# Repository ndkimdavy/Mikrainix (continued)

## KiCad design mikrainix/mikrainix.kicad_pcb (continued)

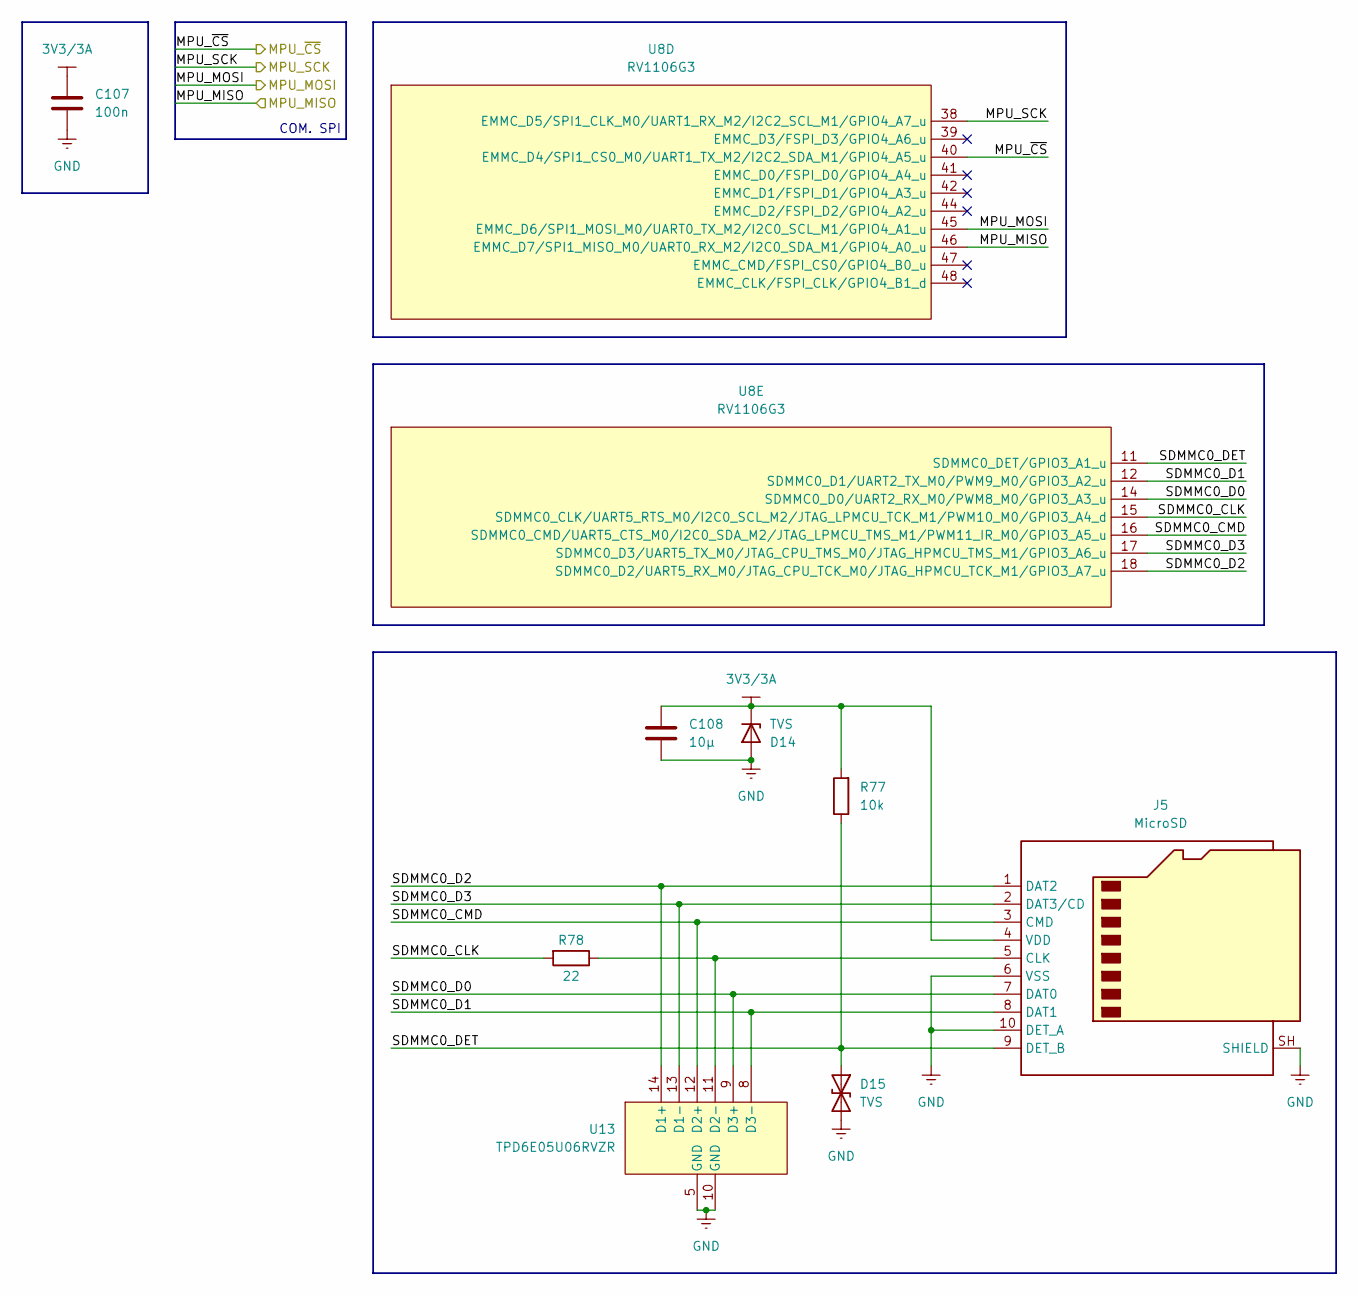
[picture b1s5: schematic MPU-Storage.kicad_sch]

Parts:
C107: 100n; C_0402_1005Metric
C108: 10µ; C_0805_2012Metric
D14: TVS; D_SMB; MPN SMLVT3V3
D15: TVS; DIO_TPD1E10B06DPYR; MPN TPD1E10B06DPYR
J5: MicroSD; microSD_HC_Hirose_DM3AT-SF-PEJM5
R77: 10k; R_0402_1005Metric
R78: 22; R_0402_1005Metric
U8: RV1106G3; QFN35P1230X1230X90-129N
U13: TPD6E05U06RVZR; RVZ0014A

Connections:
3V3/3A: C107.1, C108.1, D14.1 (K), J5.4 (VDD), R77.2; also elsewhere on the board
/U_FPGA-Ctrl/FPGA_MISO: U8.46 (EMMC_D7/SPI1_MISO_M0/UART0_RX_M2/I2C0_S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); also elsewhere on the board
/U_FPGA-Ctrl/FPGA_MOSI: U8.45 (EMMC_D6/SPI1_MOSI_M0/UART0_TX_M2/I2C0_S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); also elsewhere on the board
/U_FPGA-Ctrl/FPGA_SCK: U8.38 (EMMC_D5/SPI1_CLK_M0/UART1_RX_M2/I2C2_SC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); also elsewhere on the board
/U_FPGA-Ctrl/FPGA_~CS: U8.40 (EMMC_D4/SPI1_CS0_M0/UART1_TX_M2/I2C2_SD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); also elsewhere on the board
/U_MPU-Storage/SDMMC0_CLK: R78.2, U8.15 (SDMMC0_CLK/UART5_RTS_M0/I2C0_SCL_M2/JTA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)
/U_MPU-Storage/SDMMC0_CMD: J5.3 (CMD), U8.16 (SDMMC0_CMD/UART5_CTS_M0/I2C0_SDA_M2/JTA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), U13.12 (D2+)
/U_MPU-Storage/SDMMC0_D0: J5.7 (DAT0), U8.14 (SDMMC0_D0/UART2_RX_M0/PWM8_M0/GPIO3_A3_u), U13.9 (D3+)
/U_MPU-Storage/SDMMC0_D1: J5.8 (DAT1), U8.12 (SDMMC0_D1/UART2_TX_M0/PWM9_M0/GPIO3_A2_u), U13.8 (D3-)
/U_MPU-Storage/SDMMC0_D2: J5.1 (DAT2), U8.18 (SDMMC0_D2/UART5_RX_M0/JTAG_CPU_TCK_M0/J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), U13.14 (D1+)
/U_MPU-Storage/SDMMC0_D3: J5.2 (DAT3/CD), U8.17 (SDMMC0_D3/UART5_TX_M0/JTAG_CPU_TMS_M0/J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), U13.13 (D1-)
/U_MPU-Storage/SDMMC0_DET: D15.1 (A1), J5.9 (DET_B), R77.1, U8.11 (SDMMC0_DET/GPIO3_A1_u)
GND: C107.2, C108.2, D14.2 (A), D15.2 (A2), J5.6 (VSS), J5.10 (DET_A), J5.SH (SHIELD), U13.5 (GND), U13.10 (GND); also elsewhere on the board
unnamed: J5.5 (CLK), R78.1, U13.11 (D2-)

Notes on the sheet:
COM. SPI

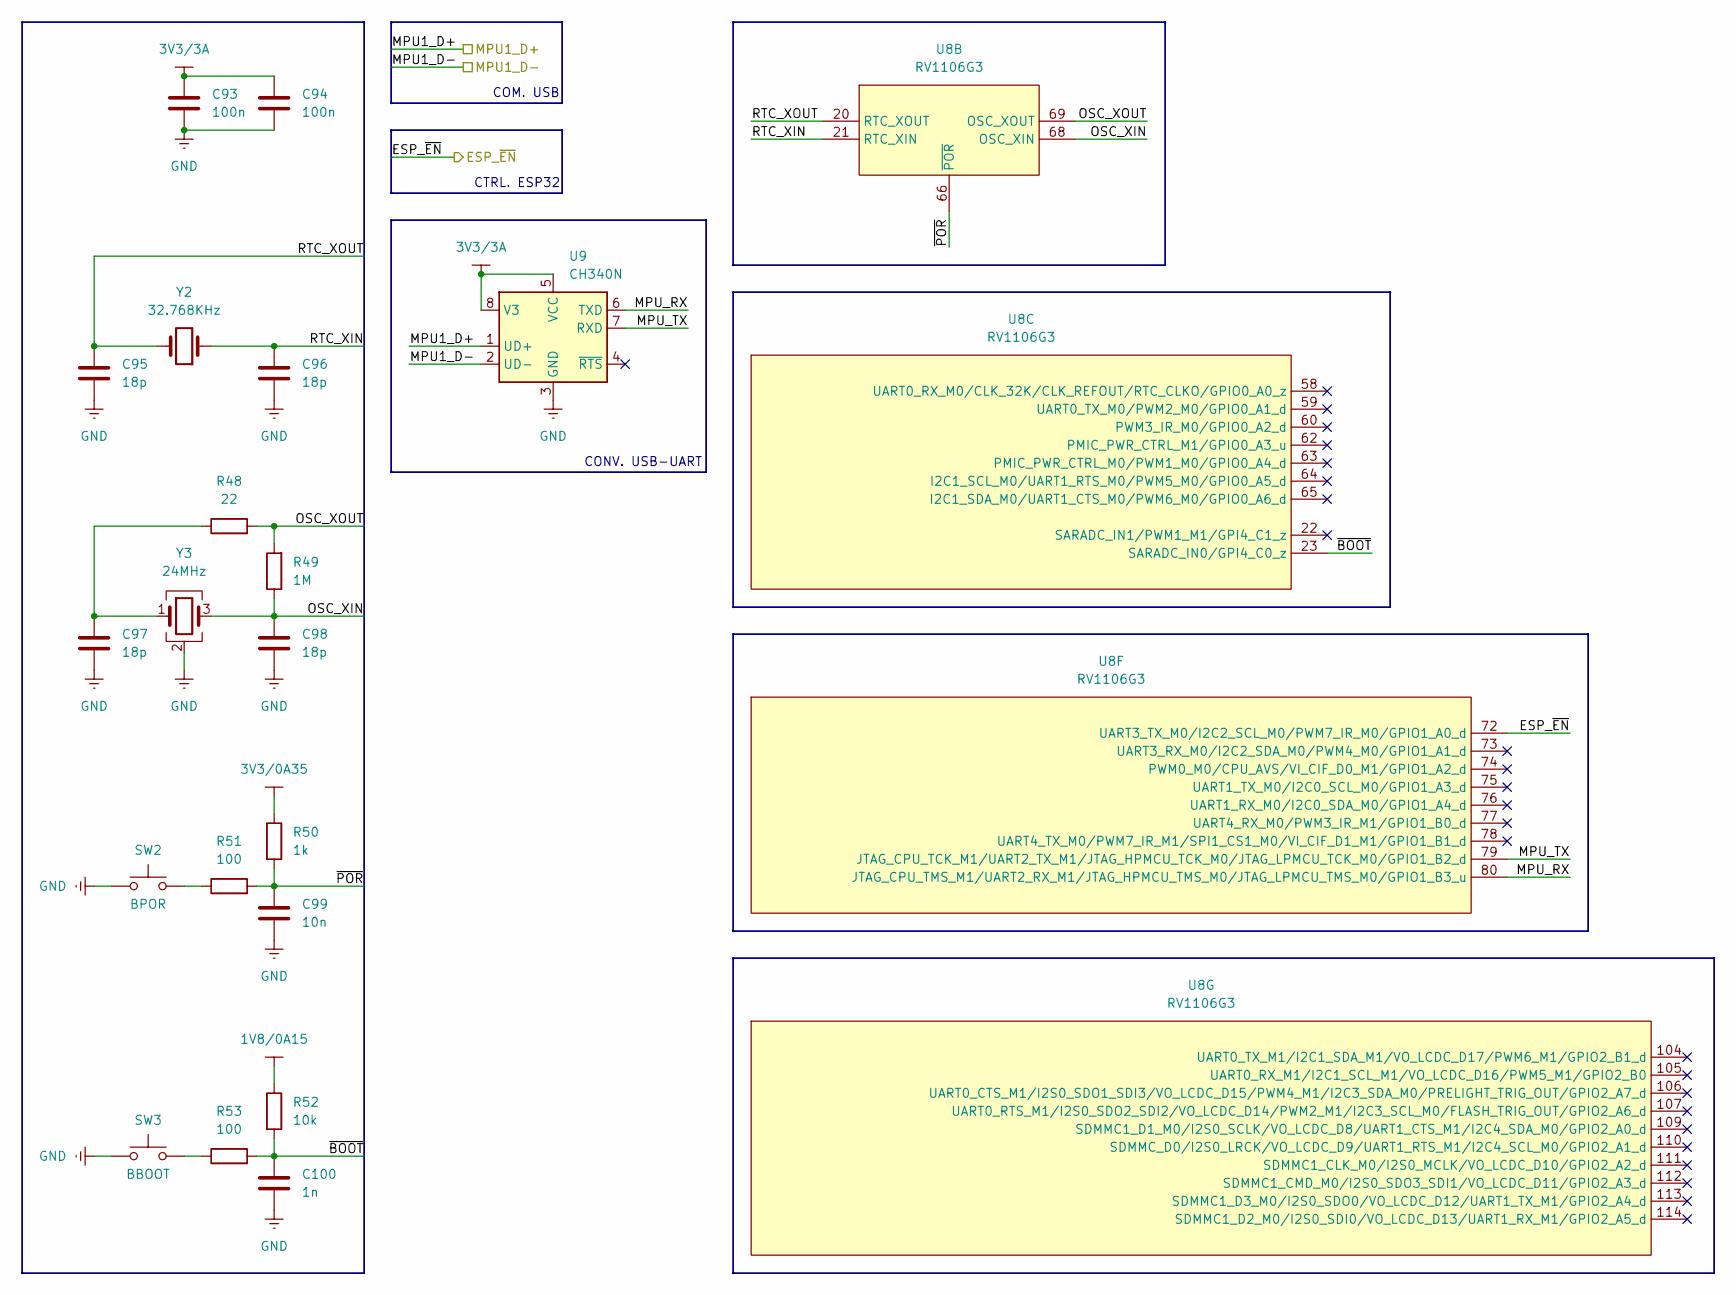
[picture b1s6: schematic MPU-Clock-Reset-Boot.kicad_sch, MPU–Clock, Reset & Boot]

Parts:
C93, C94: 100n; C_0402_1005Metric
C95, C96, C97, C98: 18p; C_0402_1005Metric; MPN GRM1555C1H180JA01D
C99: 10n; C_0402_1005Metric
C100: 1n; C_0402_1005Metric
R48: 22; R_0402_1005Metric
R49: 1M; R_0402_1005Metric
R50: 1k; R_0402_1005Metric
R51, R53: 100; R_0402_1005Metric
R52: 10k; R_0402_1005Metric
SW2: BPOR; SW_Push_1P1T_NO_CK_KMR2
SW3: BBOOT; SW_Push_1P1T_NO_CK_KMR2
U8: RV1106G3; QFN35P1230X1230X90-129N
U9: CH340N; JEITA_SOIC-8_3.9x4.9mm_P1.27mm
Y2: 32.768KHz; Crystal_SMD_3215-2Pin_3.2x1.5mm; MPN FC-135 32.7680KA-A3
Y3: 24MHz; Crystal_SMD_3225-4Pin_3.2x2.5mm; MPN ABM8-24.000MHZ-12-B1U-T

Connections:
1V8/0A15: R52.1; also elsewhere on the board
3V3/0A35: R50.1; also elsewhere on the board
3V3/3A: C93.1, C94.1, U9.5 (VCC), U9.8 (V3); also elsewhere on the board
/U_MPU-Clock-Reset-Boot-Gpio/ESP_~EN: U8.72 (UART3_TX_M0/I2C2_SCL_M0/PWM7_IR_M0/GPIO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); also elsewhere on the board
/U_MPU-Clock-Reset-Boot-Gpio/MPU1_D+: U9.1 (UD+); also elsewhere on the board
/U_MPU-Clock-Reset-Boot-Gpio/MPU1_D-: U9.2 (UD-); also elsewhere on the board
/U_MPU-Clock-Reset-Boot-Gpio/MPU_RX: U8.80 (JTAG_CPU_TMS_M1/UART2_RX_M1/JTAG_HPMCU_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), U9.6 (TXD)
/U_MPU-Clock-Reset-Boot-Gpio/MPU_TX: U8.79 (JTAG_CPU_TCK_M1/UART2_TX_M1/JTAG_HPMCU_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), U9.7 (RXD)
/U_MPU-Clock-Reset-Boot-Gpio/OSC_XIN: C98.1, R49.1, U8.68 (OSC_XIN), Y3.3
/U_MPU-Clock-Reset-Boot-Gpio/OSC_XOUT: R48.2, R49.2, U8.69 (OSC_XOUT)
/U_MPU-Clock-Reset-Boot-Gpio/RTC_XIN: C96.1, U8.21 (RTC_XIN), Y2.1
/U_MPU-Clock-Reset-Boot-Gpio/RTC_XOUT: C95.1, U8.20 (RTC_XOUT), Y2.2
/U_MPU-Clock-Reset-Boot-Gpio/~BOOT: C100.1, R52.2, R53.2, U8.23 (SARADC_IN0/GPI4_C0_z)
/U_MPU-Clock-Reset-Boot-Gpio/~POR: C99.1, R50.2, R51.2, U8.66 (~POR)
GND: C93.2, C94.2, C95.2, C96.2, C97.2, C98.2, C99.2, C100.2, SW2.1, SW3.1, U9.3 (GND), Y3.2 (G), Y3.4 (G); also elsewhere on the board
unnamed: C97.1, R48.1, Y3.1
unnamed: R51.1, SW2.2
unnamed: R53.1, SW3.2

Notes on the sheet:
CONV. USB-UART
COM. USB
CTRL. ESP32

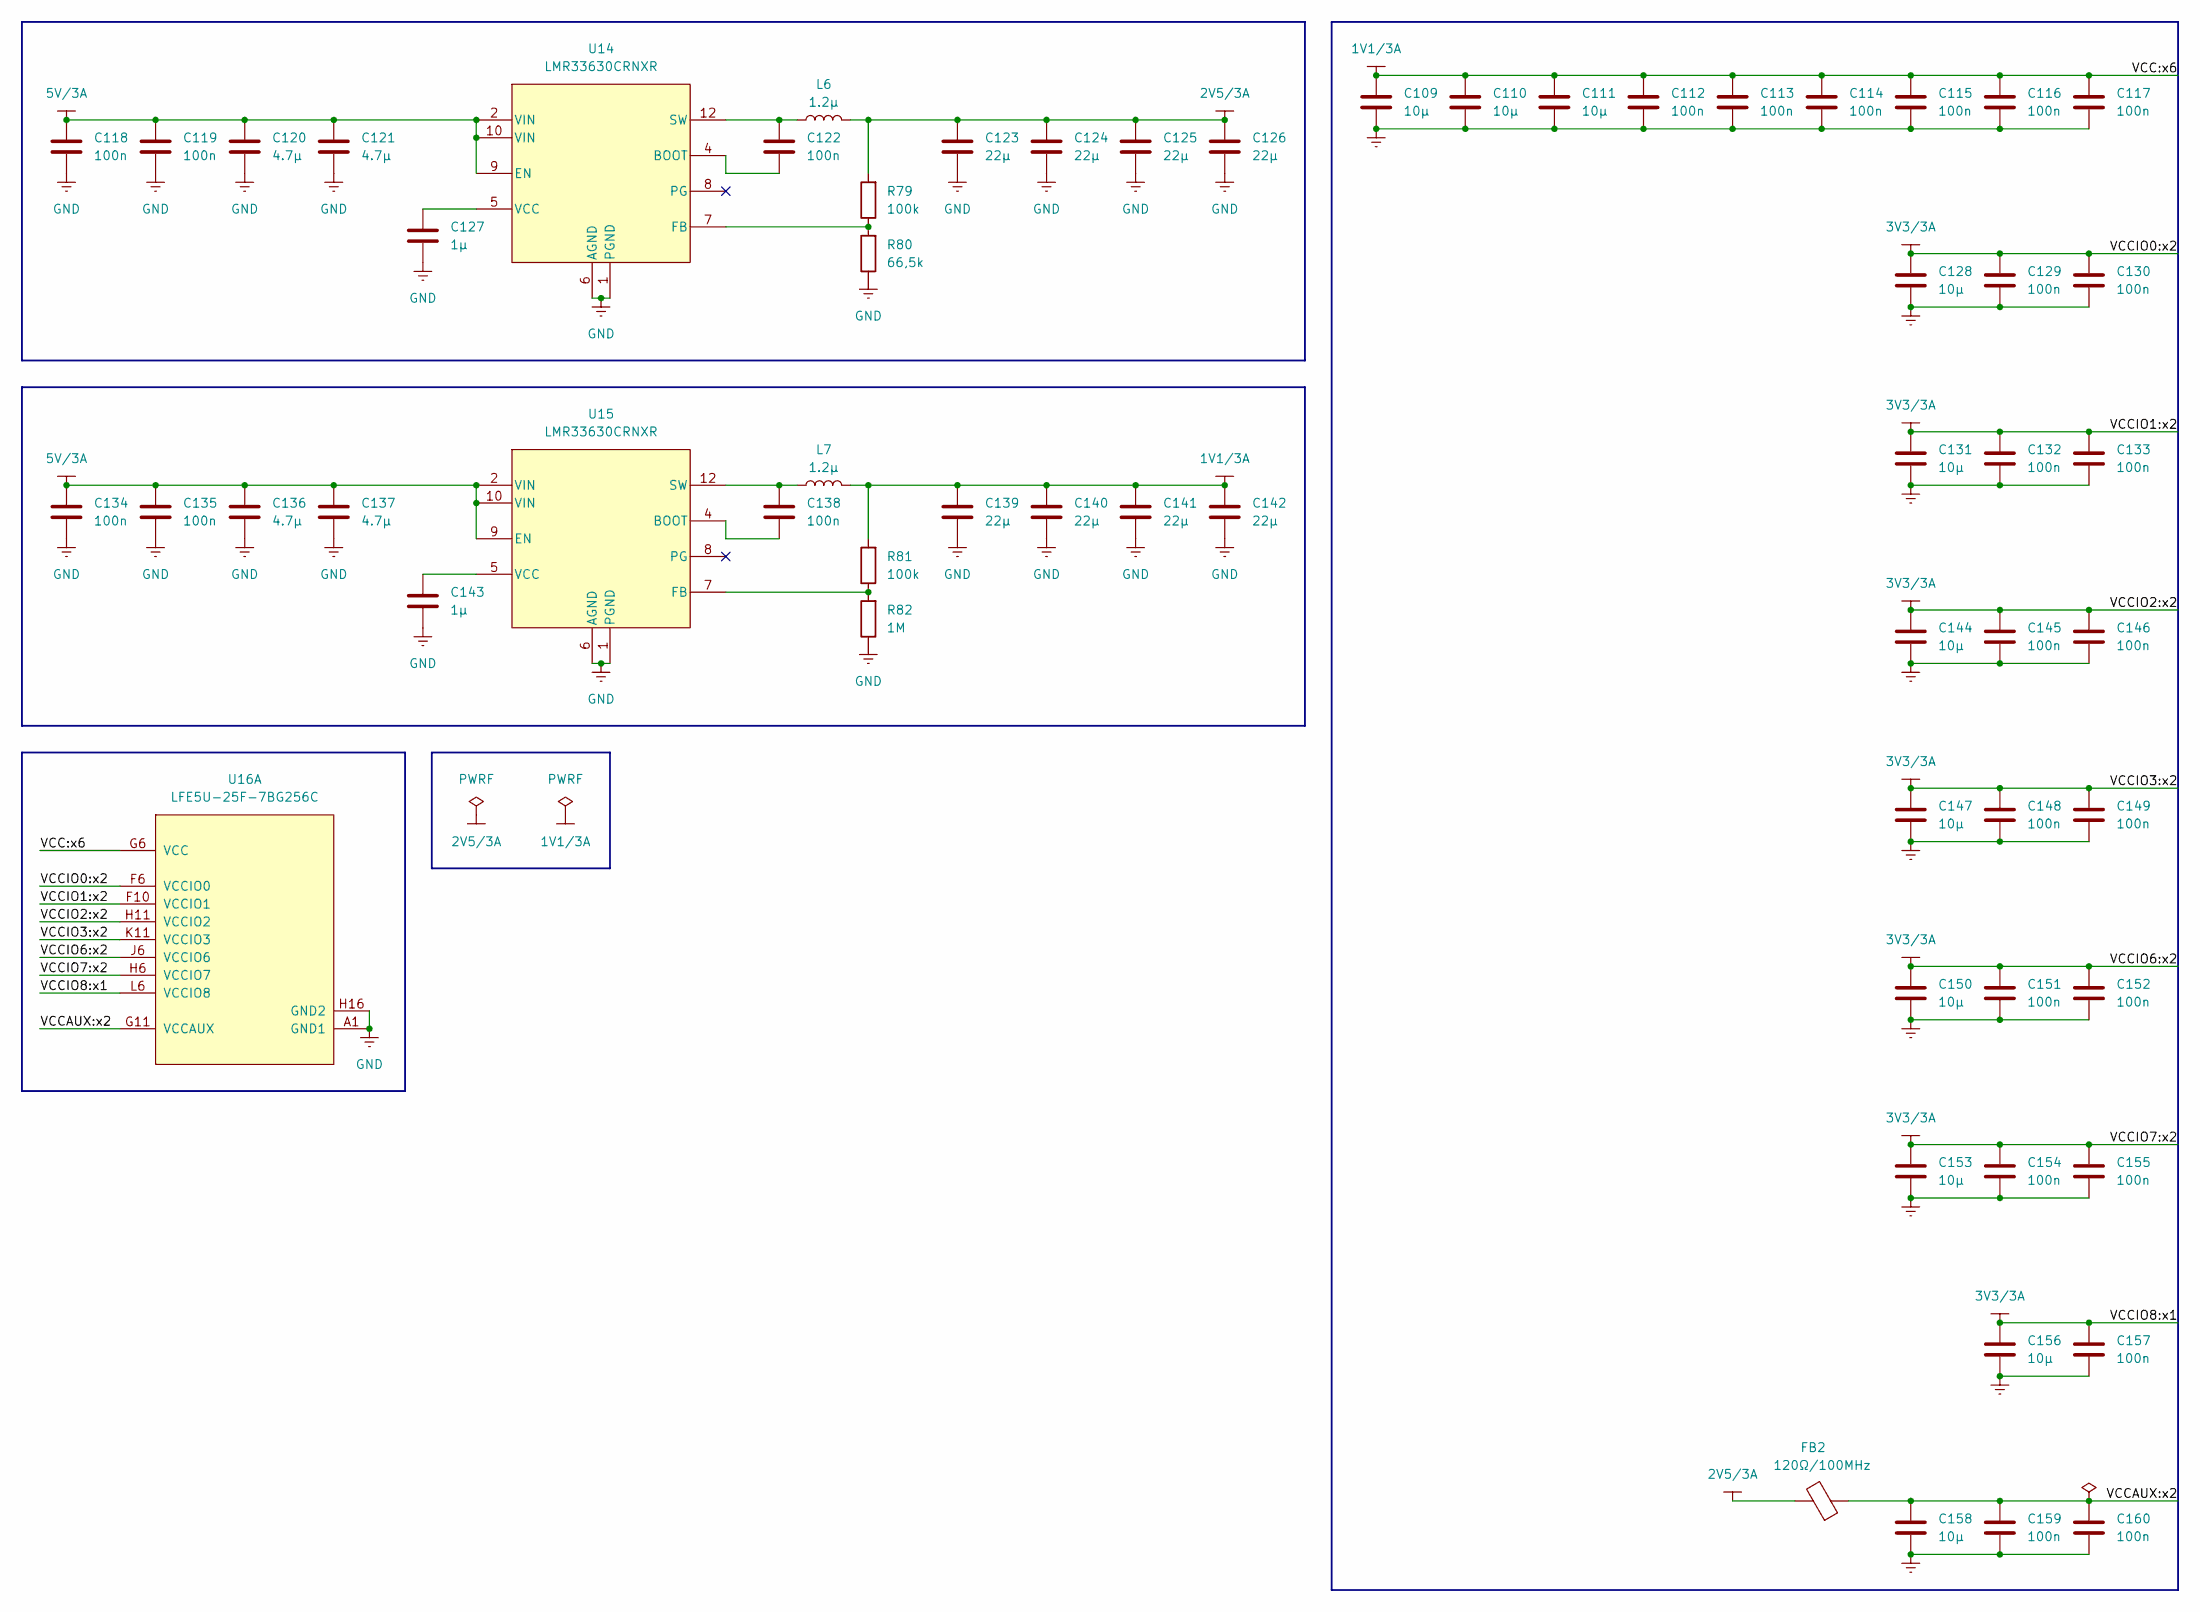
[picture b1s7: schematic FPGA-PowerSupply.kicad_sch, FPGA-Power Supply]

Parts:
C109, C110, C111, C128, C131, C144, C147, C150, C153, C156, C158: 10µ; C_0805_2012Metric
C112, C113, C114, C115, C116, C117, C129, C130, C132, C133, C145, C146, C148, C149, C151, C152, C154, C155, C157, C159, C160: 100n; C_0402_1005Metric
C118, C119, C122, C134, C135, C138: 100n; C_0603_1608Metric
C120, C121, C136, C137: 4.7µ; C_1210_3225Metric
C123, C124, C125, C126, C139, C140, C141, C142: 22µ; C_1210_3225Metric
C127, C143: 1µ; C_0805_2012Metric
FB2: 120Ω/100MHz; L_0805_2012Metric; MPN BLM21PG121SN1D
L6, L7: 1.2µ; L_Bourns_SRP5030T
R79, R81: 100k; R_0603_1608Metric
R80: 66,5k; R_0603_1608Metric
R82: 1M; R_0603_1608Metric
U14, U15: LMR33630CRNXR; RNX0012B
U16: LFE5U-25F-7BG256C; BGA-256_14.0x14.0mm_Layout16x16_P0.8mm_Ball0.45mm_Pad0.32mm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

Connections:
1V1/3A: C109.1, C110.1, C111.1, C112.1, C113.1, C114.1, C115.1, C116.1, C117.1, C139.1, C140.1, C141.1, C142.1, L7.2, R81.2, U16.G6 (VCC), U16.G7 (VCC), U16.G9 (VCC), U16.L8 (VCC), U16.L9 (VCC), U16.L10 (VCC)
2V5/3A: C123.1, C124.1, C125.1, C126.1, FB2.2, L6.2, R79.2
3V3/3A: C128.1, C129.1, C130.1, C131.1, C132.1, C133.1, C144.1, C145.1, C146.1, C147.1, C148.1, C149.1, C150.1, C151.1, C152.1, C153.1, C154.1, C155.1, C156.1, C157.1, U16.F6 (VCCIO0), U16.F7 (VCCIO0), U16.F10 (VCCIO1), U16.F11 (VCCIO1), U16.H6 (VCCIO7), U16.H7 (VCCIO7), U16.H11 (VCCIO2), U16.J6 (VCCIO6), U16.J7 (VCCIO6), U16.J11 (VCCIO2), U16.K11 (VCCIO3), U16.L6 (VCCIO8), U16.L11 (VCCIO3); also elsewhere on the board
5V/3A: C118.1, C119.1, C120.1, C121.1, C134.1, C135.1, C136.1, C137.1, U14.2 (VIN), U14.9 (EN), U14.10 (VIN), U15.2 (VIN), U15.9 (EN), U15.10 (VIN); also elsewhere on the board
GND: C109.2, C110.2, C111.2, C112.2, C113.2, C114.2, C115.2, C116.2, C117.2, C118.2, C119.2, C120.2, C121.2, C123.2, C124.2, C125.2, C126.2, C127.2, C128.2, C129.2, C130.2, C131.2, C132.2, C133.2, C134.2, C135.2, C136.2, C137.2, C139.2, C140.2, C141.2, C142.2, C143.2, C144.2, C145.2, C146.2, C147.2, C148.2, C149.2, C150.2, C151.2, C152.2, C153.2, C154.2, C155.2, C156.2, C157.2, C158.2, C159.2, C160.2, R80.1, R82.1, U14.1 (PGND), U14.6 (AGND), U14.11 (PGND), U15.1 (PGND), U15.6 (AGND), U15.11 (PGND), U16.A1 (GND1), U16.A16 (GND1), U16.D2 (GND1), U16.D15 (GND1), U16.F8 (GND1), U16.F9 (GND1), U16.G8 (GND1), U16.G10 (GND1), U16.H1 (GND1), U16.H8 (GND1), U16.H9 (GND1), U16.H10 (GND1), U16.H16 (GND2), U16.J8 (GND2), U16.J9 (GND2), U16.J10 (GND2), U16.K6 (GND2), U16.K7 (GND2), U16.K8 (GND2), U16.K9 (GND2), U16.K10 (GND2), U16.N2 (GND2), U16.N15 (GND2), U16.T1 (GND2), U16.T5 (GND2), U16.T12 (GND2), U16.T16 (GND2); also elsewhere on the board
unnamed: C122.2, U14.4 (BOOT)
unnamed: R79.1, R80.2, U14.7 (FB)
unnamed: C122.1, L6.1, U14.3 (NC), U14.12 (SW)
unnamed: C127.1, U14.5 (VCC)
unnamed: C138.2, U15.4 (BOOT)
unnamed: R81.1, R82.2, U15.7 (FB)
unnamed: C138.1, L7.1, U15.3 (NC), U15.12 (SW)
unnamed: C143.1, U15.5 (VCC)
VCCAUX: C158.1, C159.1, C160.1, FB2.1, U16.G11 (VCCAUX), U16.L7 (VCCAUX)

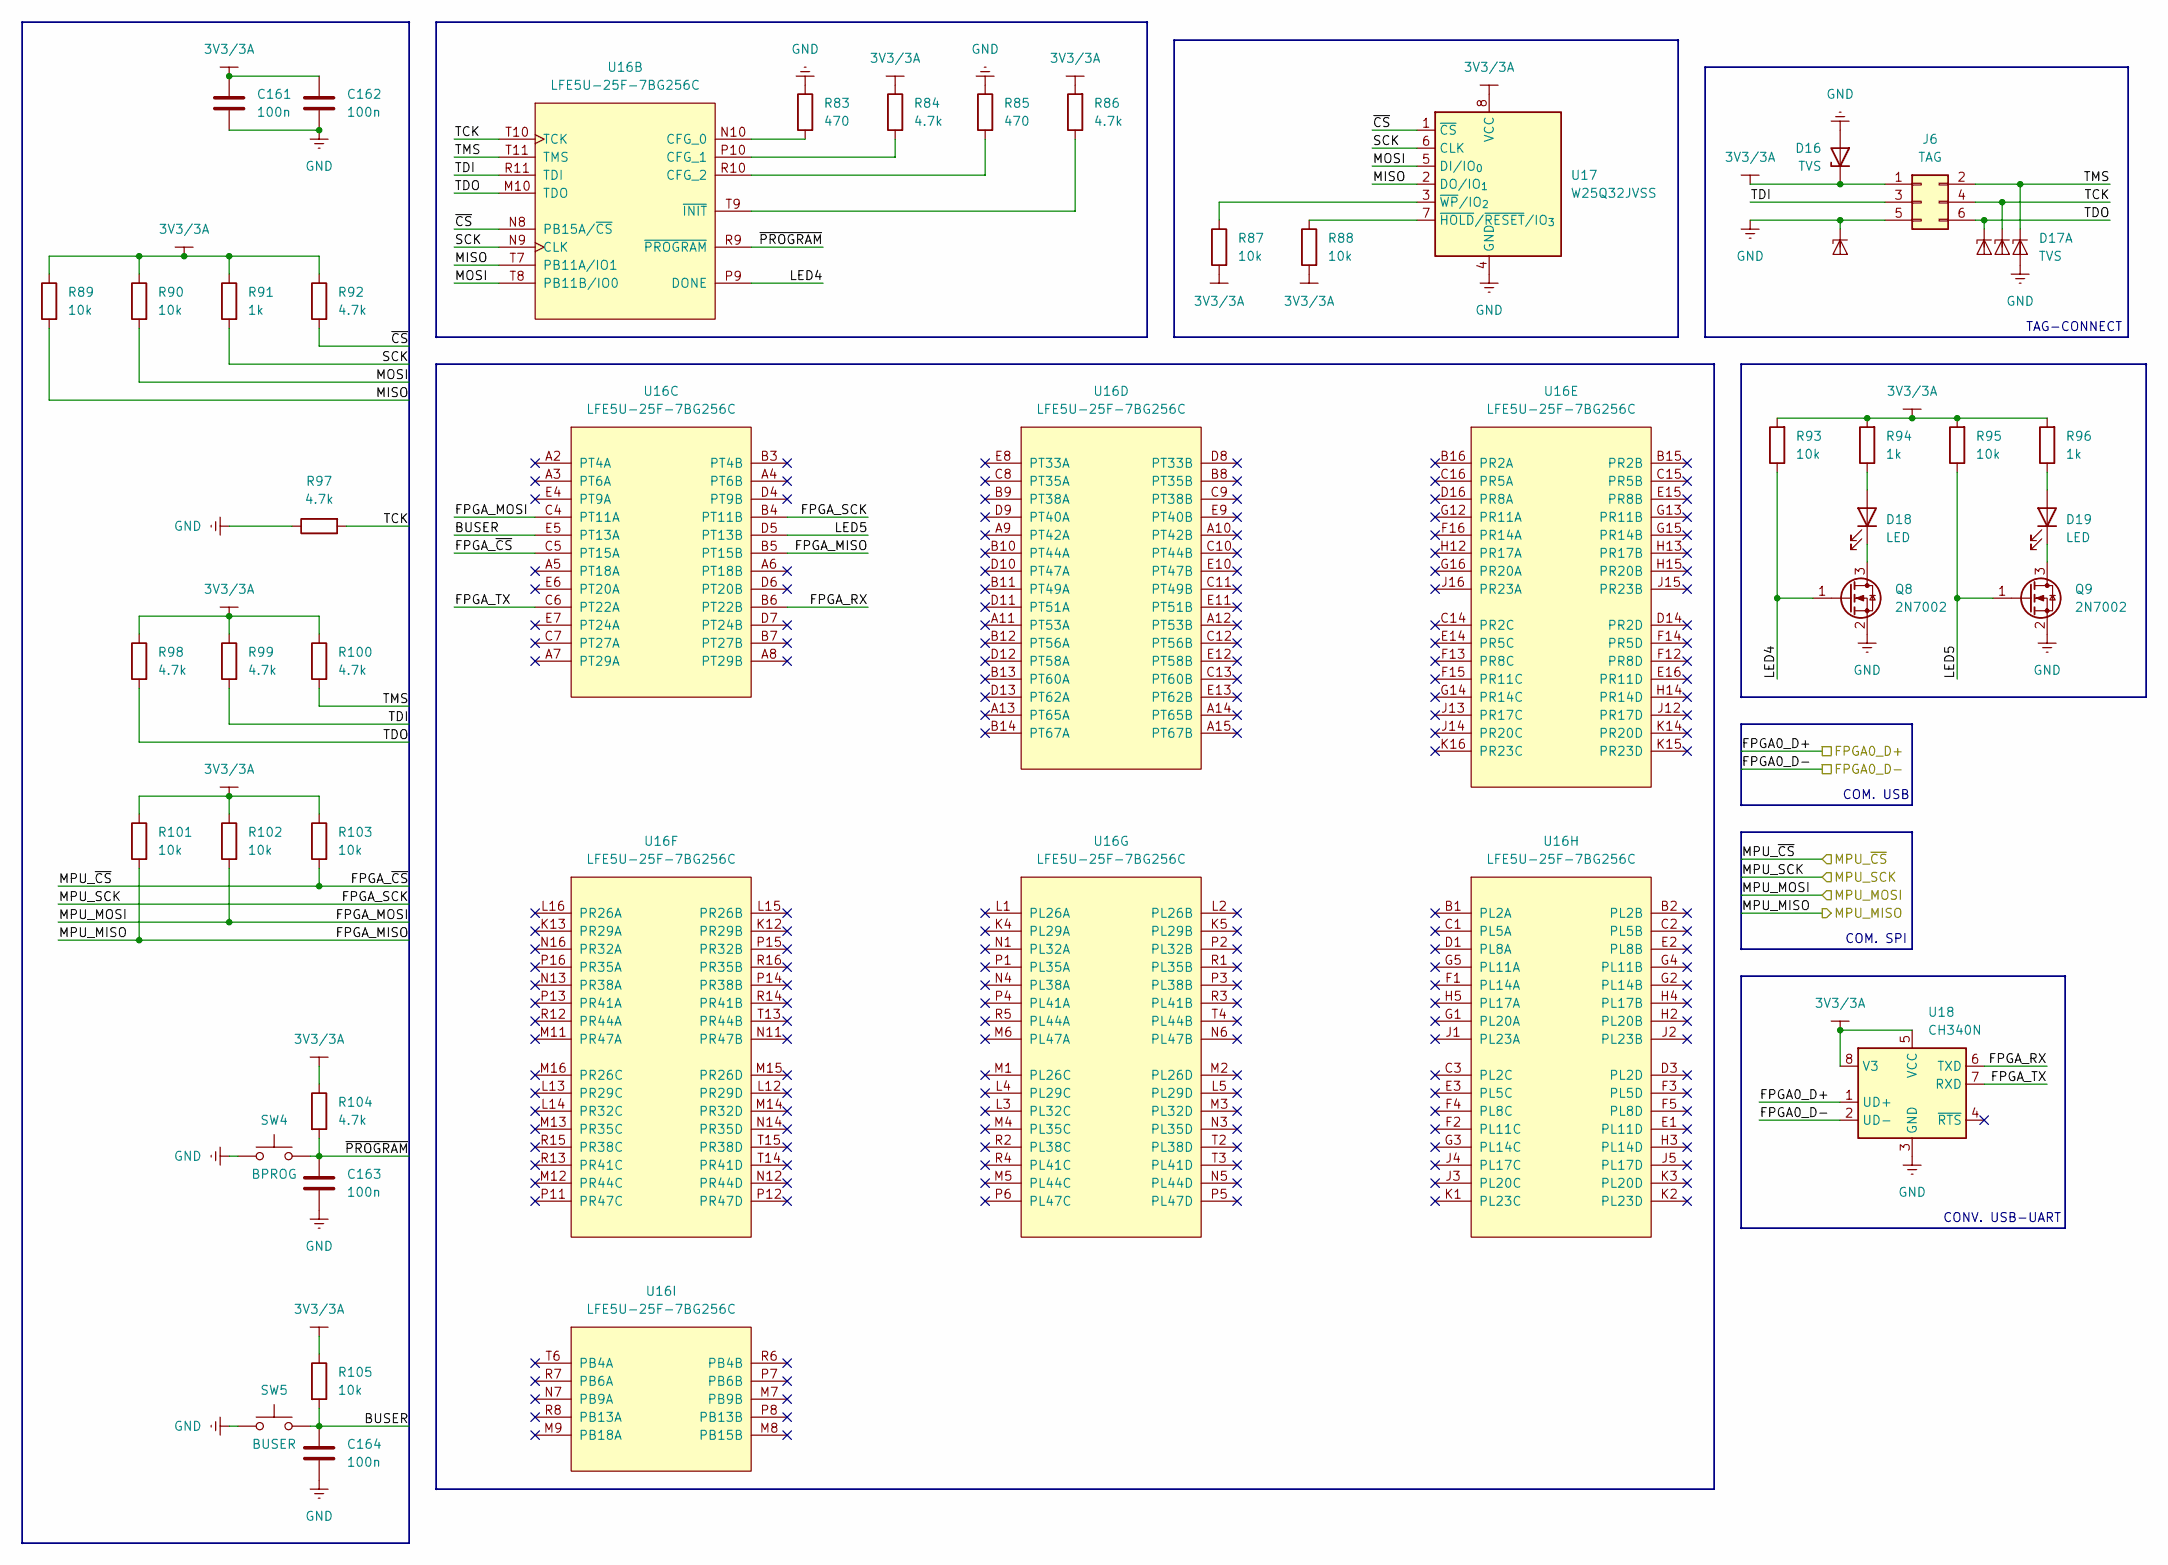
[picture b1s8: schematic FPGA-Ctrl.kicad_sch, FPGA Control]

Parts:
C161, C162, C163, C164: 100n; C_0402_1005Metric
D16: TVS; D_SMB; MPN SMLVT3V3
D17: TVS; SOT-353_SC-70-5; MPN ESDALC6V1W5
D18, D19: LED; LED_0603_1608Metric
J6: TAG; Tag-Connect_TC2030-IDC-NL_2x03_P1.27mm_Vertical; MPN TC2030-IDC-NL
Q8, Q9: 2N7002; SOT-23
R83, R85: 470; R_0402_1005Metric
R84, R86, R92, R97, R98, R99, R100, R104: 4.7k; R_0402_1005Metric
R87, R88, R89, R90, R93, R95, R101, R102, R103, R105: 10k; R_0402_1005Metric
R91, R94, R96: 1k; R_0402_1005Metric
SW4: BPROG; SW_Push_1P1T_NO_CK_KMR2
SW5: BUSER; SW_Push_1P1T_NO_CK_KMR2
U16: LFE5U-25F-7BG256C; BGA-256_14.0x14.0mm_Layout16x16_P0.8mm_Ball0.45mm_Pad0.32mm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
U17: W25Q32JVSS; SOIC-8_5.3x5.3mm_P1.27mm
U18: CH340N; JEITA_SOIC-8_3.9x4.9mm_P1.27mm

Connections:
3V3/3A: C161.1, C162.1, D16.1 (K), J6.1, R84.1, R86.2, R87.2, R88.2, R89.1, R90.1, R91.1, R92.1, R93.2, R94.2, R95.2, R96.2, R98.1, R99.1, R100.1, R101.1, R102.1, R103.1, R104.1, R105.1, U17.8 (VCC), U18.5 (VCC), U18.8 (V3); also elsewhere on the board
/U_FPGA-Ctrl/BUSER: C164.1, R105.2, SW5.2, U16.E5 (PT13A)
/U_FPGA-Ctrl/FPGA0_D+: U18.1 (UD+); also elsewhere on the board
/U_FPGA-Ctrl/FPGA0_D-: U18.2 (UD-); also elsewhere on the board
/U_FPGA-Ctrl/FPGA_MISO: R101.2, U16.B5 (PT15B); also elsewhere on the board
/U_FPGA-Ctrl/FPGA_MOSI: R102.2, U16.C4 (PT11A); also elsewhere on the board
/U_FPGA-Ctrl/FPGA_RX: U16.B6 (PT22B), U18.6 (TXD)
/U_FPGA-Ctrl/FPGA_SCK: U16.B4 (PT11B); also elsewhere on the board
/U_FPGA-Ctrl/FPGA_TX: U16.C6 (PT22A), U18.7 (RXD)
/U_FPGA-Ctrl/FPGA_~CS: R103.2, U16.C5 (PT15A); also elsewhere on the board
/U_FPGA-Ctrl/LED4: Q8.1 (G), R93.1, U16.P9 (DONE)
/U_FPGA-Ctrl/LED5: Q9.1 (G), R95.1, U16.D5 (PT13B)
/U_FPGA-Ctrl/MISO: R89.2, U16.T7 (PB11A/IO1), U17.2 (DO/IO_{1})
/U_FPGA-Ctrl/MOSI: R90.2, U16.T8 (PB11B/IO0), U17.5 (DI/IO_{0})
/U_FPGA-Ctrl/SCK: R91.2, U16.N9 (CLK), U17.6 (CLK)
/U_FPGA-Ctrl/TCK: D17.3 (K2), J6.4, R97.2, U16.T10 (TCK)
/U_FPGA-Ctrl/TDI: J6.3, R99.2, U16.R11 (TDI)
/U_FPGA-Ctrl/TDO: D17.4 (K3), J6.6, R98.2, U16.M10 (TDO)
/U_FPGA-Ctrl/TMS: D17.1 (K1), J6.2, R100.2, U16.T11 (TMS)
/U_FPGA-Ctrl/~CS: R92.2, U16.N8 (PB15A/~CS), U17.1 (~CS)
/U_FPGA-Ctrl/~PROGRAM: C163.1, R104.2, SW4.2, U16.R9 (~PROGRAM)
GND: C161.2, C162.2, C163.2, C164.2, D16.2 (A), D17.2 (A), D17.5 (K4), J6.5, Q8.2 (S), Q9.2 (S), R83.1, R85.1, R97.1, SW4.1, SW5.1, U17.4 (GND), U18.3 (GND); also elsewhere on the board
unnamed: D18.2 (A), R94.1
unnamed: D18.1 (K), Q8.3 (D)
unnamed: D19.2 (A), R96.1
unnamed: D19.1 (K), Q9.3 (D)
unnamed: R83.2, U16.N10 (CFG_0)
unnamed: R84.2, U16.P10 (CFG_1)
unnamed: R85.2, U16.R10 (CFG_2)
unnamed: R86.1, U16.T9 (~INIT)
unnamed: R88.1, U17.7 (~HOLD/~RESET/IO_{3})
unnamed: R87.1, U17.3 (~WP/IO_{2})

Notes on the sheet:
CONV. USB-UART
COM. SPI
TAG-CONNECT
COM. USB

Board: 6 copper layers, 343 parts (19 on the bottom side), 179 nets, no tracks yet.

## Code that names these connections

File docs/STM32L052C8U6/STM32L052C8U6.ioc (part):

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Mcu.Name=STM32L052C(6-8)Ux
Mcu.Package=UFQFPN48
Mcu.UserName=STM32L052C8Ux
PA10.Mode=Asynchronous
PA10.Signal=USART1_RX
PA11.Mode=Device
PA11.Signal=USB_DM
PA12.Mode=Device
PA12.Signal=USB_DP
PA13.Mode=Serial_Wire
PA13.Signal=SYS_SWDIO
PA14.Mode=Serial_Wire
PA14.Signal=SYS_SWCLK
PA15.GPIOParameters=GPIO_Label
PA15.GPIO_Label=LED0
PA15.Signal=GPIO_Output
PA2.Mode=Asynchronous
PA2.Signal=USART2_TX
PA3.Mode=Asynchronous
PA3.Signal=USART2_RX
PA9.Mode=Asynchronous
PA9.Signal=USART1_TX
PB5.Mode=SMBus-Alert-mode
PB5.Signal=I2C1_SMBA
PB6.Mode=SMBus-Alert-mode
PB6.Signal=I2C1_SCL
PB7.Mode=SMBus-Alert-mode
PB7.Signal=I2C1_SDA
PC13.Mode=SYS_WakeUp1
PC13.Signal=SYS_WKUP2
PH0-OSC_IN.Mode=HSE-External-Oscillator
PH0-OSC_IN.Signal=RCC_OSC_IN
PH1-OSC_OUT.Mode=HSE-External-Oscillator
PH1-OSC_OUT.Signal=RCC_OSC_OUT
RCC.HSE_VALUE=16000000
RCC.SYSCLKFreq_VALUE=16000000
RCC.SYSCLKSource=RCC_SYSCLKSOURCE_HSE
board=custom
